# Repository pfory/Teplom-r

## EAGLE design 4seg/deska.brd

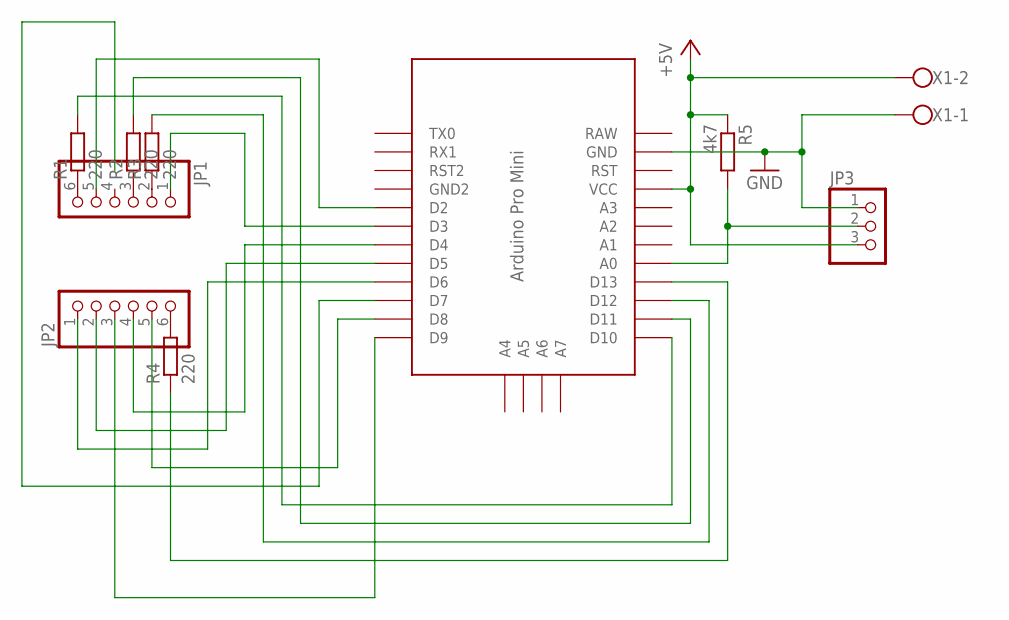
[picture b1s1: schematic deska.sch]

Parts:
JP1, JP2: PINHD-1X6; 1X06
JP3: PINHD-1X3; 1X03
R1, R2, R3, R4: 220; 0204/7
R5: 4k7; 0204/7
U$1: PRO-MINI
X1: W237-102

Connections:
+5V: JP3.3, R5.1, U$1.VCC, X1.2
GND: JP3.1, U$1.GND, X1.1
unnamed: JP1.6, R1.1
unnamed: JP1.3, R2.1
unnamed: JP1.2, R3.1
unnamed: JP2.6, R4.2
unnamed: R1.2, U$1.D10
unnamed: R2.2, U$1.D11
unnamed: R3.2, U$1.D12
unnamed: R4.1, U$1.D13
unnamed: JP1.5, U$1.D2
unnamed: JP1.1, U$1.D3
unnamed: JP2.4, U$1.D4
unnamed: JP2.2, U$1.D5
unnamed: JP2.1, U$1.D6
unnamed: JP2.5, U$1.D8
unnamed: JP2.3, U$1.D9
unnamed: JP3.2, R5.2, U$1.A0
RAW: U$1.RAW

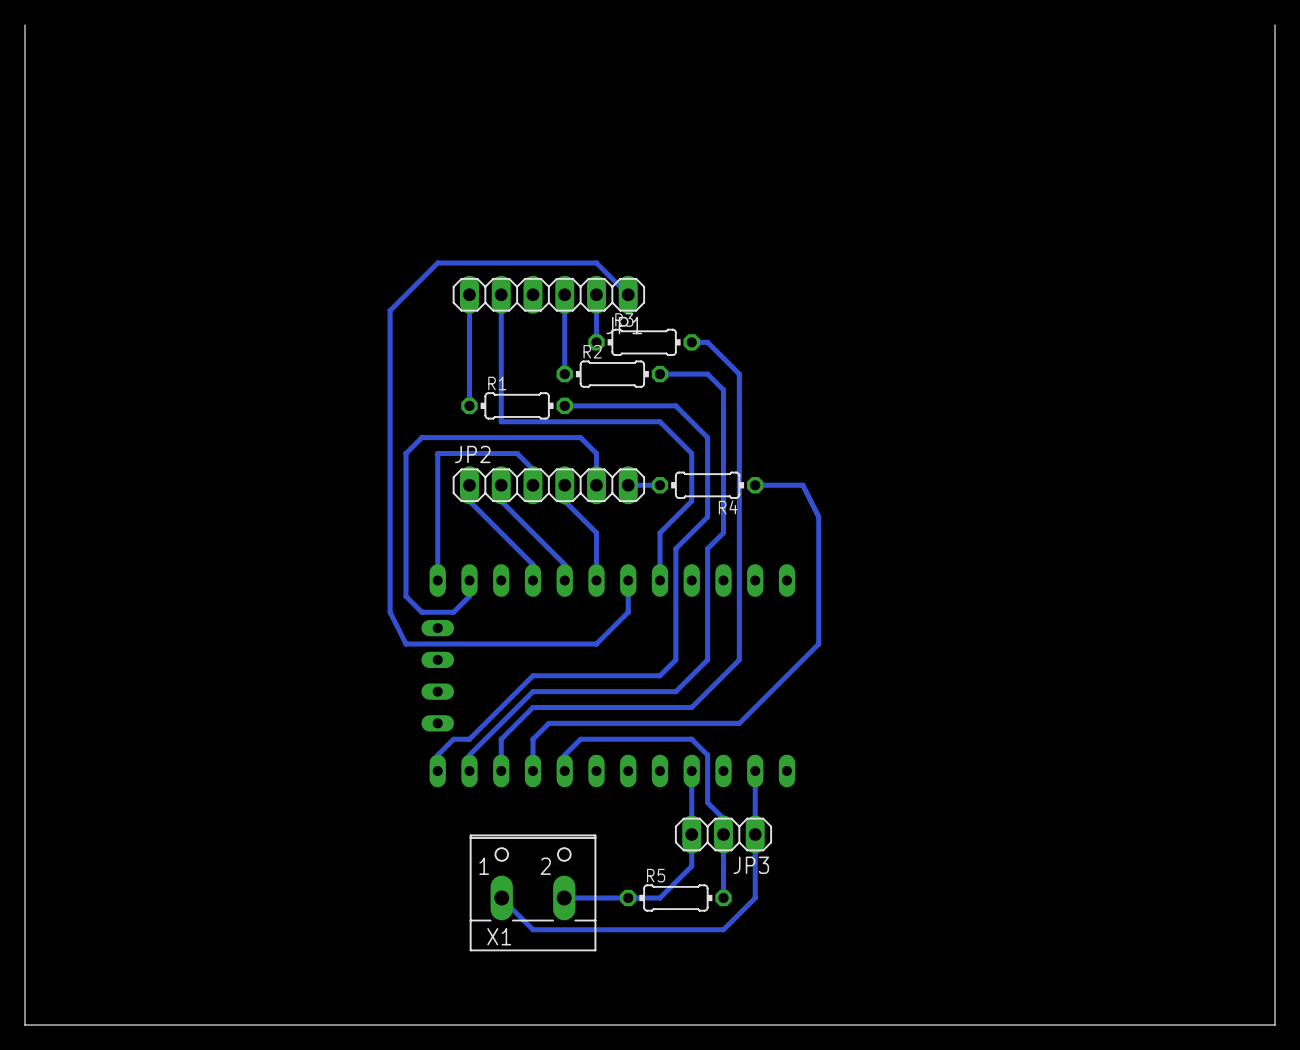
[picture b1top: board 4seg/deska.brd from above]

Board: 2 copper layers, 100.0 x 80.0 mm, 10 parts (0 on the bottom side), 18 nets.

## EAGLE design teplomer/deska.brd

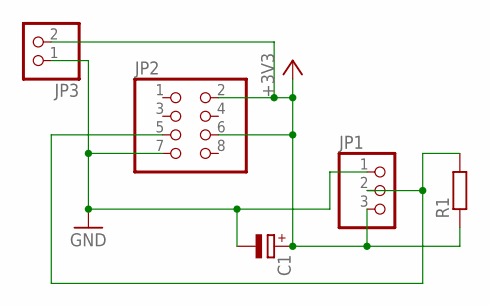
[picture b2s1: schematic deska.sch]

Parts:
C1: CPOL-EUE3.5-8; E3,5-8
JP1: PINHD-1X3; 1X03
JP2: PINHD-2X4; 2X04
JP3: PINHD-1X2; 1X02
R1: R-EU_0204/7; 0204/7

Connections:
+3V3: C1.+, JP1.3, JP2.2, JP2.6, JP3.2, R1.1
GND: C1.-, JP1.1, JP2.7, JP3.1
unnamed: JP1.2, JP2.5, R1.2

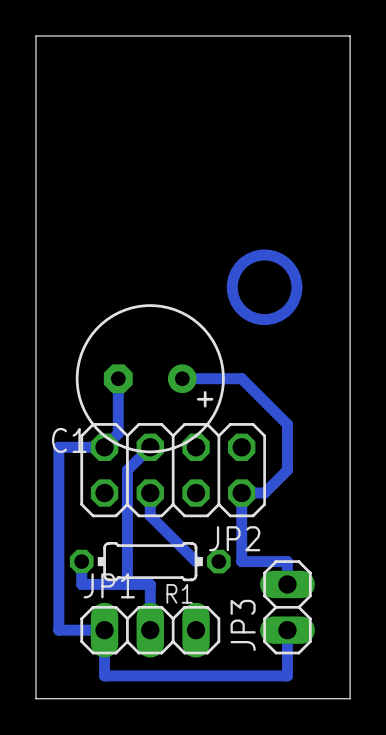
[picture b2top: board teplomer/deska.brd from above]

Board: 2 copper layers, 17.4 x 36.8 mm, 5 parts (0 on the bottom side), 3 nets.

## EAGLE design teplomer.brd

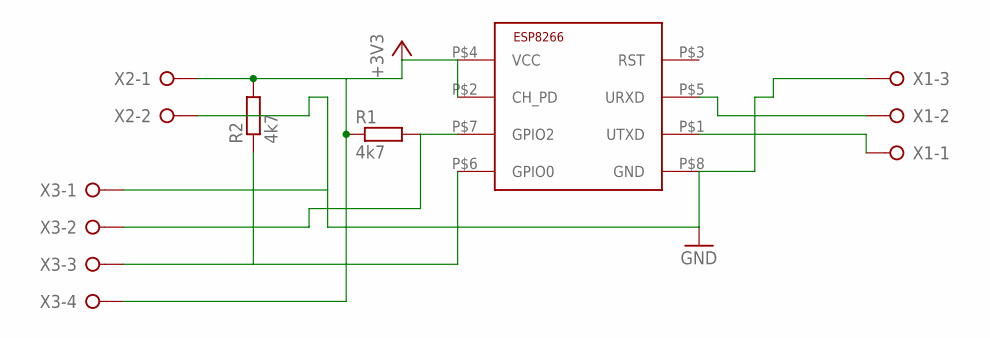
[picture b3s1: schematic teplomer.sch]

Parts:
R1, R2: 4k7; 0204/5
U$1: ESP8266-01; ESP-01
X1: W237-3E
X2: W237-02P; W237-132
X3: W237-04P; W237-4P

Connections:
+3V3: R1.1, R2.2, U$1.P$2 (CH_PD), U$1.P$4 (VCC), X2.1, X3.4
GND: U$1.P$8 (GND), X1.3, X2.2, X3.1
unnamed: U$1.P$5 (URXD), X1.2
unnamed: U$1.P$1 (UTXD), X1.1
unnamed: R2.1, U$1.P$6 (GPIO0), X3.3
unnamed: R1.2, U$1.P$7 (GPIO2), X3.2

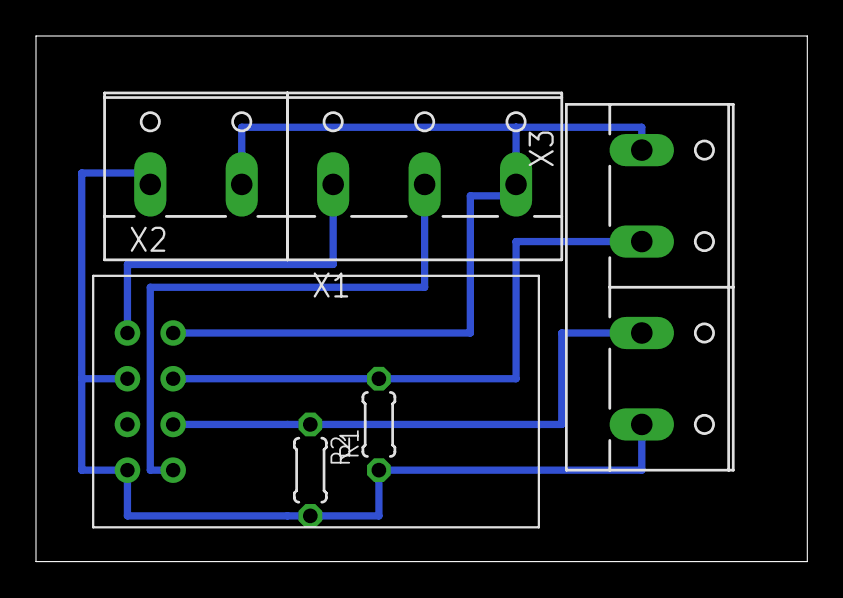
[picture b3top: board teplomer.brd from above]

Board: 2 copper layers, 42.9 x 29.2 mm, 6 parts (0 on the bottom side), 6 nets.

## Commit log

2016-03-20 initial version
2016-03-22 +fw This was built against the master branch and includes the following modules: file, gpio, mqtt, net, node, ow, tmr, uart, wifi.
2016-03-30 +identifikace resetu +zmena verze +vyhodnocení teplot nil
2016-04-02 v02 chata 2.4.2016
2016-04-20 +schenma
2016-04-26 +rozliseni bootreason
2016-04-26 v0.35
2016-04-27 +drobna zmena, nema vliv na fungovani
2016-05-04 +novejsi verze knihovny
2016-05-25 v0.4 + reconnect each 10 minutes
2016-05-25 +gitignore
2016-05-26 +autoreconnect
2016-06-04 v0,5
2016-07-26 pi on chata
2016-10-19 prvni pokus s konfiguracnim souborem
2016-12-01 pocet meridel na 7
2016-12-07 funkcni verze
2016-12-08 zobrazeni adres DS
2017-01-10 +ino
2017-10-11 Create teplomerKvasnaNadoba
    +projekt mereni teploty pro kvasnou nadobu
2017-10-11 Rename teplomerKvasnaNadoba to teplomerKvasnaNadoba.ino
    pridana pripona ino
2017-10-12 dopleno HB a verze
2018-01-11 teplomer pro jeden dallas
2018-02-14 +deska
2018-08-27 v0.61
2018-10-30 v0.7
2019-03-07 json 6 ota.sh
2019-03-07 v0.72
2019-03-07 -sender
